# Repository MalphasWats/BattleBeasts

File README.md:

# BattleBeasts

![PCBWAY][PCBWAYLOGO]

Just before Christmas, I had a kind offer from the folks at [PCBWay][PCBWAY] to work on a small maker project. I saw this as a great opportunity to experiment with some new tech and designed a new board around the Microchip SAMD21G microcontroller.

I've always wanted to build a 'Tamagotchi'-type device, so I designed a simple development board the size of a standard playing card with an 8x8 LED matrix and some capacitative-touch buttons. I knocked my design up in KiCAD in a couple of hours:

![KiCAD PCB Layout][KiCAD]

and uploaded the files to the PCB website.

Not long afterwards I got these beauties in the post:

![PCBWay PCBs][BOARDS]

I'd also asked for a solder paste stencil. I was a little bit lazy and just added a comment for it to be made the same size as the board and the guys at PCBWay did it for me which was really great. The boards were really good quality - I poked at them with my multimeter to check continuity and everything was fine.

The black soldermask looks so good on bare PCBs.

Using some old PCBs from another project, I taped the stencil down to my workbench:

![Stencil taped to PCB][STENCIL]

and applied the paste. I think my paste might be a little bit old but it still looks good. I'd really like to get a little USB microscope so I can take proper solder paste glamour shots!

![Solder paste porn][PASTE]

I then very patiently placed most of the components - I don't have any RGB LEDs or coin cell holders so I left those off. This is easily the highest component count I've assembled so far and it went really well. I was paranoid about the LEDs being the right way around so I check every single one out of the reel-strip!

After blasting it with my hot air gun, I think it looks pretty good:

![Finished Board][FINISHED].

I can power the board via the USB connector whilst I'm developing and I can add the RGBs to it later once I've got the matrix working.

My main goal with this board is to build up my Arm MCU development toolchain so getting some code up and running is the next step!

[PCBWAY]: http://www.pcbway.com
[PCBWAYLOGO]: http://www.subdimension.co.uk/files/2020-01-10-New-Year-New-Gear/pcbway.png
[KiCAD]: http://www.subdimension.co.uk/files/2020-01-10-New-Year-New-Gear/KiCAD.png
[BOARDS]: http://www.subdimension.co.uk/files/2020-01-10-New-Year-New-Gear/boards.jpeg
[STENCIL]: http://www.subdimension.co.uk/files/2020-01-10-New-Year-New-Gear/stencil.jpeg
[PASTE]: http://www.subdimension.co.uk/files/2020-01-10-New-Year-New-Gear/paste.jpeg
[FINISHED]: http://www.subdimension.co.uk/files/2020-01-10-New-Year-New-Gear/finished.jpeg
[BB]: https://github.com/MalphasWats/BattleBeasts

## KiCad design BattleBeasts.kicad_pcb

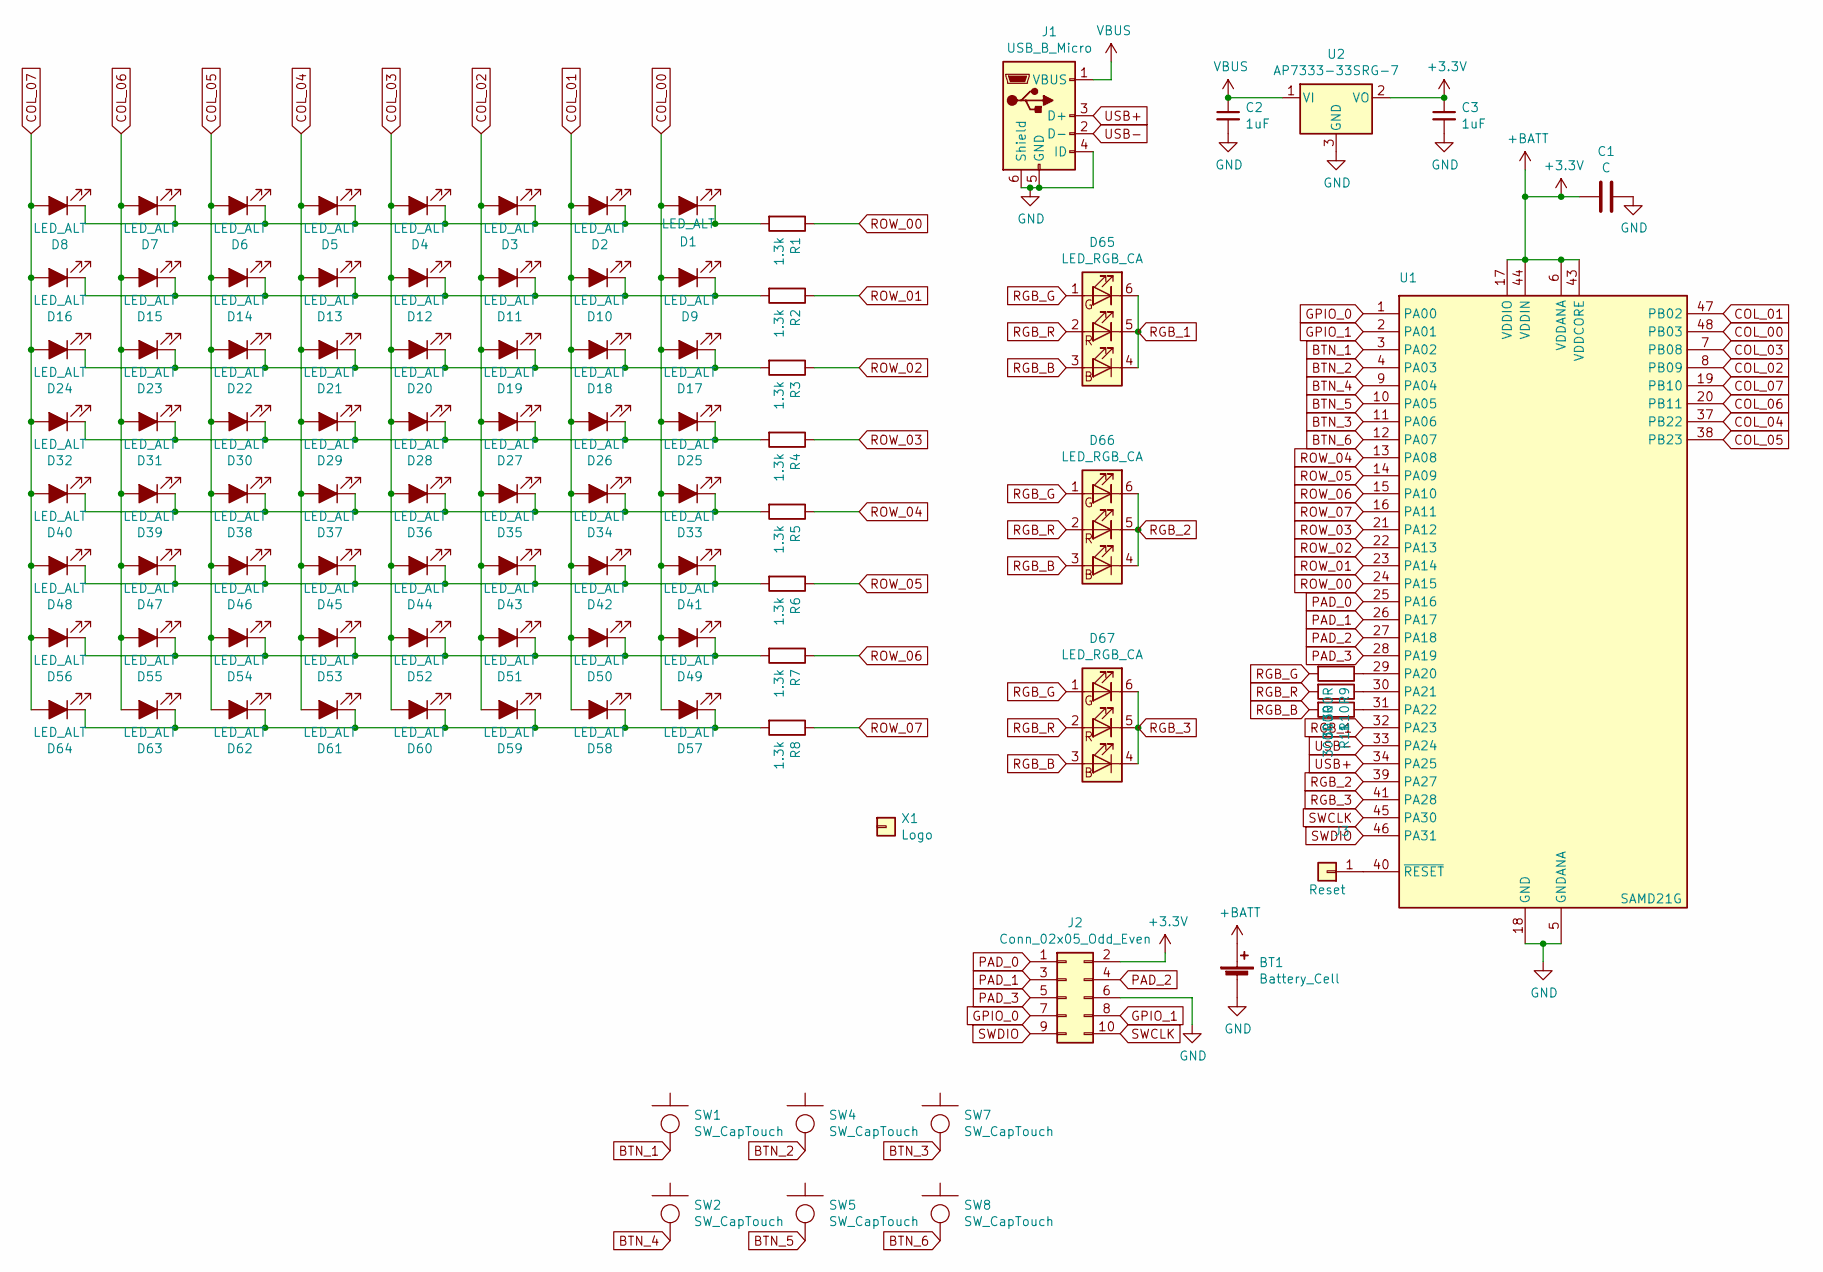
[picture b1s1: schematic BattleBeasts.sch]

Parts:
BT1: Battery_Cell; BatteryHolder_Keystone_3002_1x2032
C1: C; C_0805_2012Metric
C2, C3: 1uF; C_0805_2012Metric_Pad1.15x1.40mm_HandSolder
D1, D2, D3, D4, D5, D6, D7, D8, D9, D10, D11, D12, D13, D14, D15, D16, D17, D18, D19, D20, D21, D22, D23, D24, D25, D26, D27, D28, D29, D30, D31, D32, D33, D34, D35, D36, D37, D38, D39, D40, D41, D42, D43, D44, D45, D46, D47, D48, D49, D50, D51, D52, D53, D54, D55, D56, D57, D58, D59, D60, D61, D62, D63, D64: LED_ALT; LED_1206_3216Metric_Clean
D65, D66, D67: LED_RGB_CA; LED_Avago_PLCC6_3x2.8mm
J1: USB_B_Micro; USB_Micro-B_Molex-105017-0001
J2: Conn_02x05_Odd_Even; PinHeader_2x05_P2.54mm_Vertical
J3: Reset; TestPoint_Pad_1.0x1.0mm
R1, R2, R3, R4, R5, R6, R7, R8: 1.3k; R_0805_2012Metric
R9, R10, R11: 300R; R_0805_2012Metric
SW1, SW2, SW4, SW5, SW7, SW8: SW_CapTouch; CapTouch_D8.0mm
U1: SAMD21G; TQFP-48_7x7mm_P0.5mm
U2: AP7333-33SRG-7; SOT-23
X1: Logo; LOGO_5x5

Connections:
+3V3: BT1.1 (+), C1.2, C3.1, J2.2, U1.6 (VDDANA), U1.17 (VDDIO), U1.36 (VDDIO), U1.43 (VDDCORE), U1.44 (VDDIN), U2.2 (VO)
BTN_1: SW1.1, U1.3 (PA02)
BTN_2: SW4.1, U1.4 (PA03)
BTN_3: SW7.1, U1.11 (PA06)
BTN_4: SW2.1, U1.9 (PA04)
BTN_5: SW5.1, U1.10 (PA05)
BTN_6: SW8.1, U1.12 (PA07)
COL_00: D1.2 (A), D9.2 (A), D17.2 (A), D25.2 (A), D33.2 (A), D41.2 (A), D49.2 (A), D57.2 (A), U1.48 (PB03)
COL_01: D2.2 (A), D10.2 (A), D18.2 (A), D26.2 (A), D34.2 (A), D42.2 (A), D50.2 (A), D58.2 (A), U1.47 (PB02)
COL_02: D3.2 (A), D11.2 (A), D19.2 (A), D27.2 (A), D35.2 (A), D43.2 (A), D51.2 (A), D59.2 (A), U1.8 (PB09)
COL_03: D4.2 (A), D12.2 (A), D20.2 (A), D28.2 (A), D36.2 (A), D44.2 (A), D52.2 (A), D60.2 (A), U1.7 (PB08)
COL_04: D5.2 (A), D13.2 (A), D21.2 (A), D29.2 (A), D37.2 (A), D45.2 (A), D53.2 (A), D61.2 (A), U1.37 (PB22)
COL_05: D6.2 (A), D14.2 (A), D22.2 (A), D30.2 (A), D38.2 (A), D46.2 (A), D54.2 (A), D62.2 (A), U1.38 (PB23)
COL_06: D7.2 (A), D15.2 (A), D23.2 (A), D31.2 (A), D39.2 (A), D47.2 (A), D55.2 (A), D63.2 (A), U1.20 (PB11)
COL_07: D8.2 (A), D16.2 (A), D24.2 (A), D32.2 (A), D40.2 (A), D48.2 (A), D56.2 (A), D64.2 (A), U1.19 (PB10)
GND: BT1.2 (-), C1.1, C2.2, C3.2, J1.4 (ID), J1.5 (GND), J1.6 (Shield), J2.6, U1.5 (GNDANA), U1.18 (GND), U1.35 (GND), U1.42 (GND), U2.3 (GND)
GPIO_0: J2.7, U1.1 (PA00)
GPIO_1: J2.8, U1.2 (PA01)
unnamed: D1.1 (K), D2.1 (K), D3.1 (K), D4.1 (K), D5.1 (K), D6.1 (K), D7.1 (K), D8.1 (K), R1.2
unnamed: D9.1 (K), D10.1 (K), D11.1 (K), D12.1 (K), D13.1 (K), D14.1 (K), D15.1 (K), D16.1 (K), R2.2
unnamed: D17.1 (K), D18.1 (K), D19.1 (K), D20.1 (K), D21.1 (K), D22.1 (K), D23.1 (K), D24.1 (K), R3.2
unnamed: D25.1 (K), D26.1 (K), D27.1 (K), D28.1 (K), D29.1 (K), D30.1 (K), D31.1 (K), D32.1 (K), R4.2
unnamed: D33.1 (K), D34.1 (K), D35.1 (K), D36.1 (K), D37.1 (K), D38.1 (K), D39.1 (K), D40.1 (K), R5.2
unnamed: D41.1 (K), D42.1 (K), D43.1 (K), D44.1 (K), D45.1 (K), D46.1 (K), D47.1 (K), D48.1 (K), R6.2
unnamed: D49.1 (K), D50.1 (K), D51.1 (K), D52.1 (K), D53.1 (K), D54.1 (K), D55.1 (K), D56.1 (K), R7.2
unnamed: D57.1 (K), D58.1 (K), D59.1 (K), D60.1 (K), D61.1 (K), D62.1 (K), D63.1 (K), D64.1 (K), R8.2
unnamed: J3.1, U1.40 (~RESET)
unnamed: R9.1, U1.29 (PA20)
unnamed: R10.1, U1.30 (PA21)
unnamed: R11.1, U1.31 (PA22)
PAD_0: J2.1, U1.25 (PA16)
PAD_1: J2.3, U1.26 (PA17)
PAD_2: J2.4, U1.27 (PA18)
PAD_3: J2.5, U1.28 (PA19)
RGB_1: D65.4 (BA), D65.5 (GA), D65.6 (RA), U1.32 (PA23)
RGB_2: D66.4 (BA), D66.5 (GA), D66.6 (RA), U1.39 (PA27)
RGB_3: D67.4 (BA), D67.5 (GA), D67.6 (RA), U1.41 (PA28)
RGB_B: D65.3 (BK), D66.3 (BK), D67.3 (BK), R11.2
RGB_G: D65.1 (RK), D66.1 (RK), D67.1 (RK), R9.2
RGB_R: D65.2 (GK), D66.2 (GK), D67.2 (GK), R10.2
ROW_00: R1.1, U1.24 (PA15)
ROW_01: R2.1, U1.23 (PA14)
ROW_02: R3.1, U1.22 (PA13)
ROW_03: R4.1, U1.21 (PA12)
ROW_04: R5.1, U1.13 (PA08)
ROW_05: R6.1, U1.14 (PA09)
ROW_06: R7.1, U1.15 (PA10)
ROW_07: R8.1, U1.16 (PA11)
SWCLK: J2.10, U1.45 (PA30)
SWDIO: J2.9, U1.46 (PA31)
USB+: J1.3 (D+), U1.34 (PA25)
USB-: J1.2 (D-), U1.33 (PA24)
VBUS: C2.1, J1.1 (VBUS), U2.1 (VI)

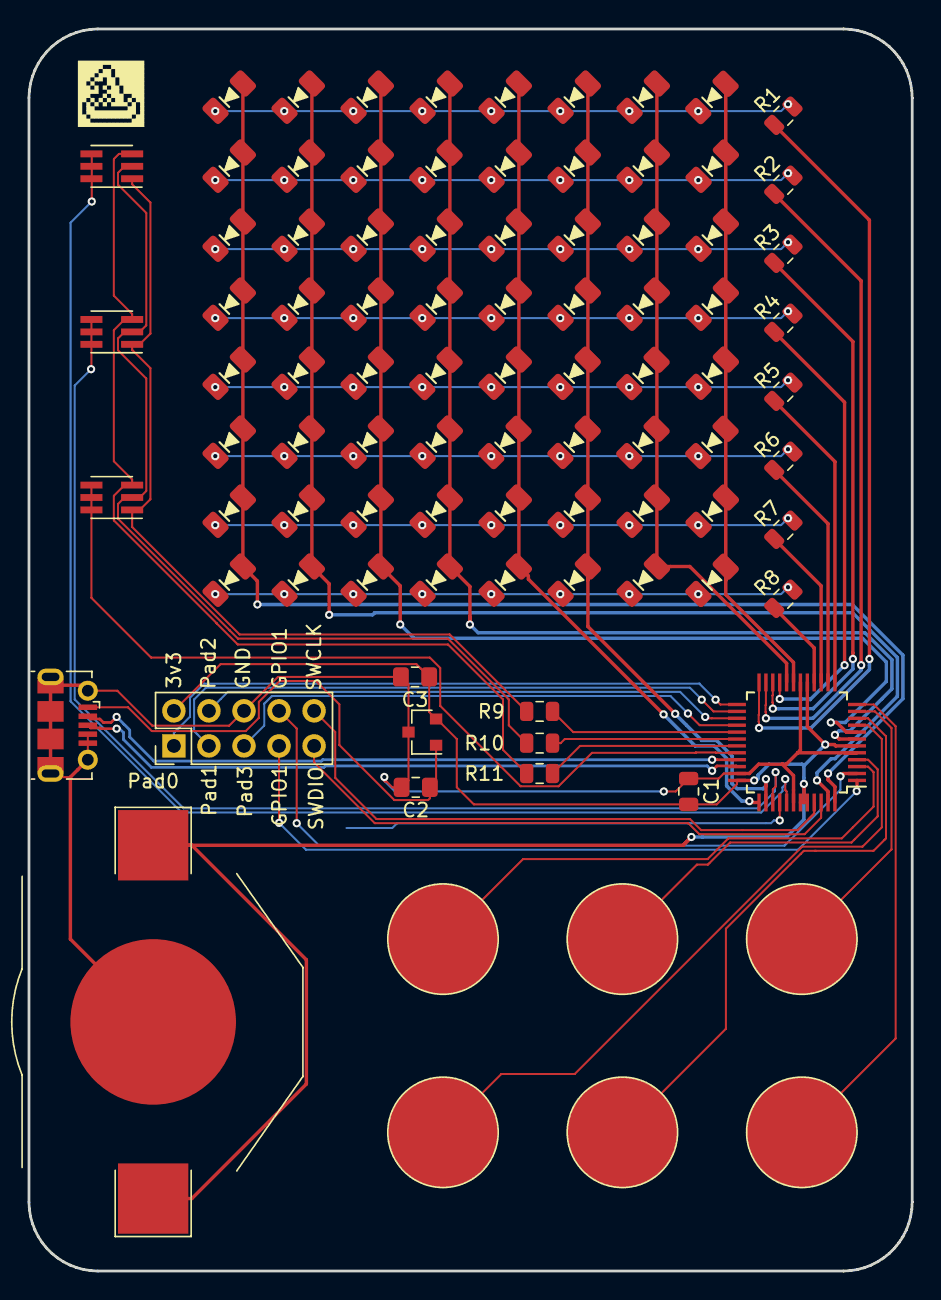
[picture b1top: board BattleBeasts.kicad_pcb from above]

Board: 2 copper layers, 64.0 x 90.0 mm, 94 parts (1 on the bottom side), 53 nets.

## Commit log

2019-02-28 Changed name
2019-03-03 initial structure
2019-03-04 use draw image function for title
2019-03-04 fixed a thing
2019-03-05 updated title
2019-03-05 make beasts
2019-03-05 generate many beasts
2019-03-05 reset beast before re-generating
2019-03-05 fixed reflection
2019-03-06 initial attempt to display beast larger
2019-03-11 fixed broken generation and scaling
2019-03-12 arbitrary scaling
2019-03-12 I'll make this mistake forever.
2019-04-30 best not to look.
2019-04-30 editors shouldn't change things at the cursor if the cursor is off screen...
2019-04-30 graphic assets
2019-11-17 BattleBeasts custom pcb idea
2019-12-30 reworking for SAMD21 version
2020-01-11 blink test
2020-01-12 Tidy code
2020-01-12 using the wrong device!
2020-01-14 Mirror blog post
